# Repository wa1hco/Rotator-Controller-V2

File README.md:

# Rotator-Controller-V2
Designed to remotely control CDE rotors. Updated design with new enclosure and optional user interface

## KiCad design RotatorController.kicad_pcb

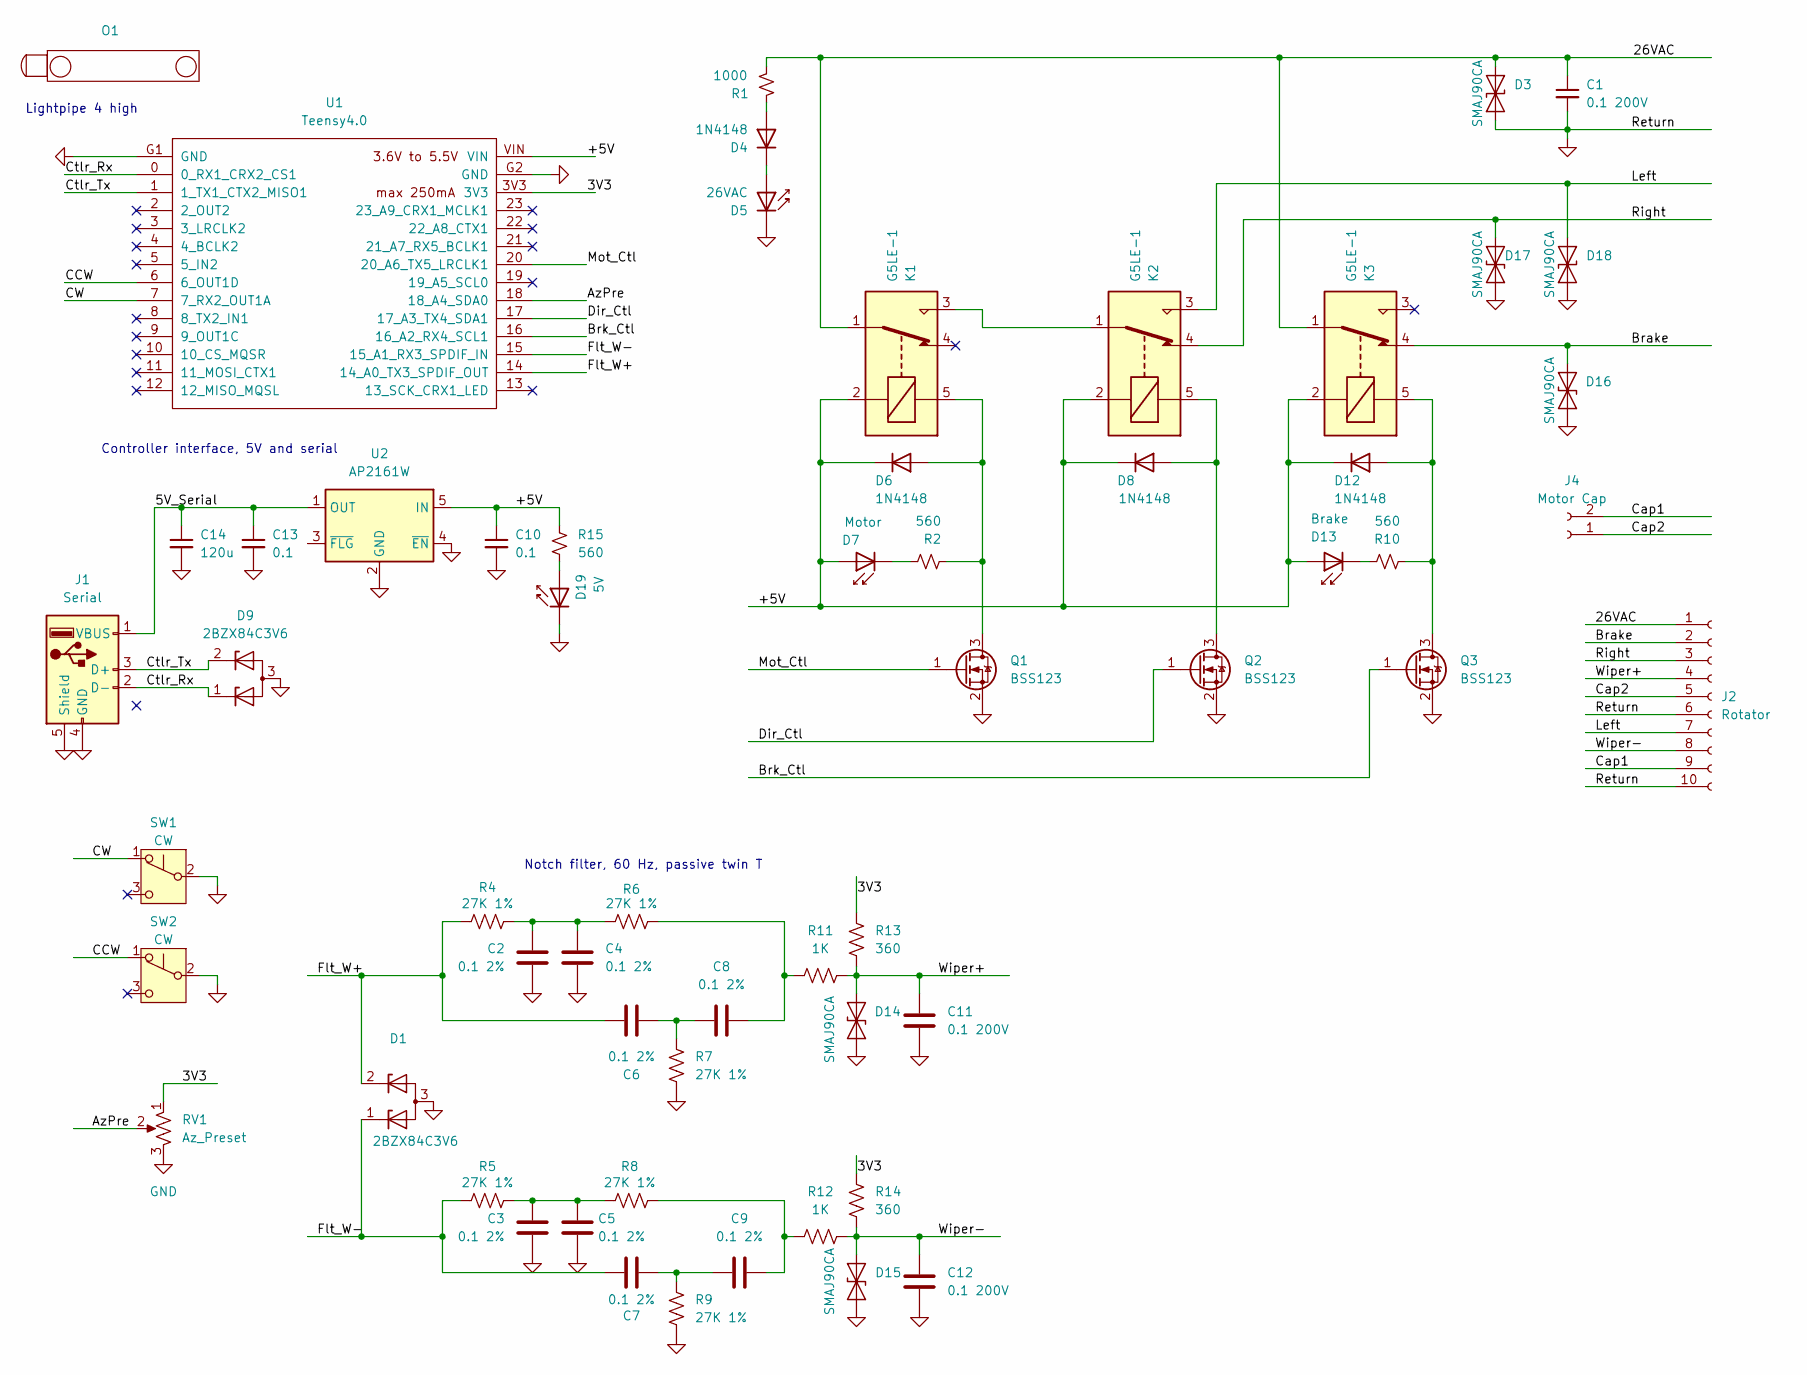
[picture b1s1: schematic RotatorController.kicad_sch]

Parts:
C1, C11, C12: 0.1 200V; C_1206_3216Metric_Pad1.33x1.80mm_HandSolder
C2, C3, C4, C5, C6, C7, C8, C9: 0.1 2%; C_1206_3216Metric_Pad1.33x1.80mm_HandSolder
C10, C13: 0.1; C_1206_3216Metric_Pad1.33x1.80mm_HandSolder
C14: 120u; C_1206_3216Metric_Pad1.33x1.80mm_HandSolder
D1, D9: 2BZX84C3V6; SOT-23
D3, D14, D15, D16, D17, D18: SMAJ90CA; D_SMA
D4, D6, D8, D12: 1N4148; D_SOD-123F
D5: 26VAC; LED_0805_2012Metric
D7: Motor; LED_0805_2012Metric
D13: Brake; LED_0805_2012Metric
D19: 5V; LED_0805_2012Metric
J1: Serial; USB_A_TE_292303-7_Horizontal
J2: Rotator; TE_MATE-N-LOK_1-770971-x_2x05_P4.14mm_Horizontal
J4: Motor Cap; PinHeader_1x02_P2.54mm_Vertical
K1, K2, K3: G5LE-1; Relay_SPDT_Omron-G5LE-1
O1: LP4-EP
Q1, Q2, Q3: BSS123; SOT-23
R1: 1000; R_0805_2012Metric_Pad1.20x1.40mm_HandSolder
R2, R10, R15: 560; R_0805_2012Metric_Pad1.20x1.40mm_HandSolder
R4, R5, R6, R7, R8, R9: 27K 1%; R_0805_2012Metric_Pad1.20x1.40mm_HandSolder
R11, R12: 1K; R_0805_2012Metric_Pad1.20x1.40mm_HandSolder
R13, R14: 360; R_0805_2012Metric_Pad1.20x1.40mm_HandSolder
RV1: Az_Preset; Potentiometer_Alps_RK09K_Single_Horizontal
SW1, SW2: CW; SW_SPST_Omron_B3F-315x_Angled
U1: Teensy4.0; Teensy40_Simple
U2: AP2161W; SOT-23-5

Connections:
/3V3: R13.1, R14.1, RV1.1, U1.3V3
/5V_Serial: C13.1, C14.1, J1.1 (VBUS), U2.1 (OUT)
/26VAC: C1.1, D3.2 (A2), J2.1, K1.1, K3.1, R1.2
/+5V: C10.1, D6.1 (K), D7.2 (A), D8.1 (K), D12.1 (K), D13.2 (A), K1.2, K2.2, K3.2, R15.2, U1.VIN, U2.5 (IN)
/AzPre: RV1.2, U1.18 (18_A4_SDA0)
/Brake: D16.2 (A2), J2.2, K3.4
/Brk_Ctl: Q3.1 (G), U1.16 (16_A2_RX4_SCL1)
/CCW: SW2.1 (A), U1.6 (6_OUT1D)
/CW: SW1.1 (A), U1.7 (7_RX2_OUT1A)
/Cap1: J2.9, J4.2
/Cap2: J2.5, J4.1
/Ctlr_Rx: D9.1 (K), J1.2 (D-), U1.0 (0_RX1_CRX2_CS1)
/Ctlr_Tx: D9.2 (K), J1.3 (D+), U1.1 (1_TX1_CTX2_MISO1)
/Dir_Ctl: Q2.1 (G), U1.17 (17_A3_TX4_SDA1)
/Flt_W+: C6.1, D1.2 (K), R4.1, U1.14 (14_A0_TX3_SPDIF_OUT)
/Flt_W-: C7.1, D1.1 (K), R5.1, U1.15 (15_A1_RX3_SPDIF_IN)
/Left: D18.2 (A2), J2.7, K2.3
/Mot_Ctl: Q1.1 (G), U1.20 (20_A6_TX5_LRCLK1)
/Right: D17.2 (A2), J2.3, K2.4
/Wiper+: C11.2, D14.2 (A2), J2.4, R11.2, R13.2
/Wiper-: C12.2, D15.2 (A2), J2.8, R12.2, R14.2
GND: C1.2, C2.2, C3.2, C4.2, C5.2, C10.2, C11.1, C12.1, C13.2, C14.2, D1.3 (A), D3.1 (A1), D5.1 (K), D9.3 (A), D14.1 (A1), D15.1 (A1), D16.1 (A1), D17.1 (A1), D18.1 (A1), D19.1 (K), J1.4 (GND), J1.5 (Shield), J2.6, J2.10, Q1.2 (S), Q2.2 (S), Q3.2 (S), R7.2, R9.2, RV1.3, SW1.2 (B), SW2.2 (B), U1.G1 (GND), U1.G2 (GND), U2.2 (GND), U2.4 (~EN)
unnamed: C2.1, C4.1, R4.2, R6.1
unnamed: C3.1, C5.1, R5.2, R8.1
unnamed: C6.2, C8.1, R7.1
unnamed: C7.2, C9.1, R9.1
unnamed: C8.2, R6.2, R11.1
unnamed: C9.2, R8.2, R12.1
unnamed: D4.2 (A), R1.1
unnamed: D4.1 (K), D5.2 (A)
unnamed: D6.2 (A), K1.5, Q1.3 (D), R2.2
unnamed: D7.1 (K), R2.1
unnamed: D8.2 (A), K2.5, Q2.3 (D)
unnamed: D12.2 (A), K3.5, Q3.3 (D), R10.2
unnamed: D13.1 (K), R10.1
unnamed: D19.2 (A), R15.1
unnamed: K1.3, K2.1

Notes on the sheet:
Controller interface, 5V and serial
Lightpipe 4 high
Notch filter, 60 Hz, passive twin T

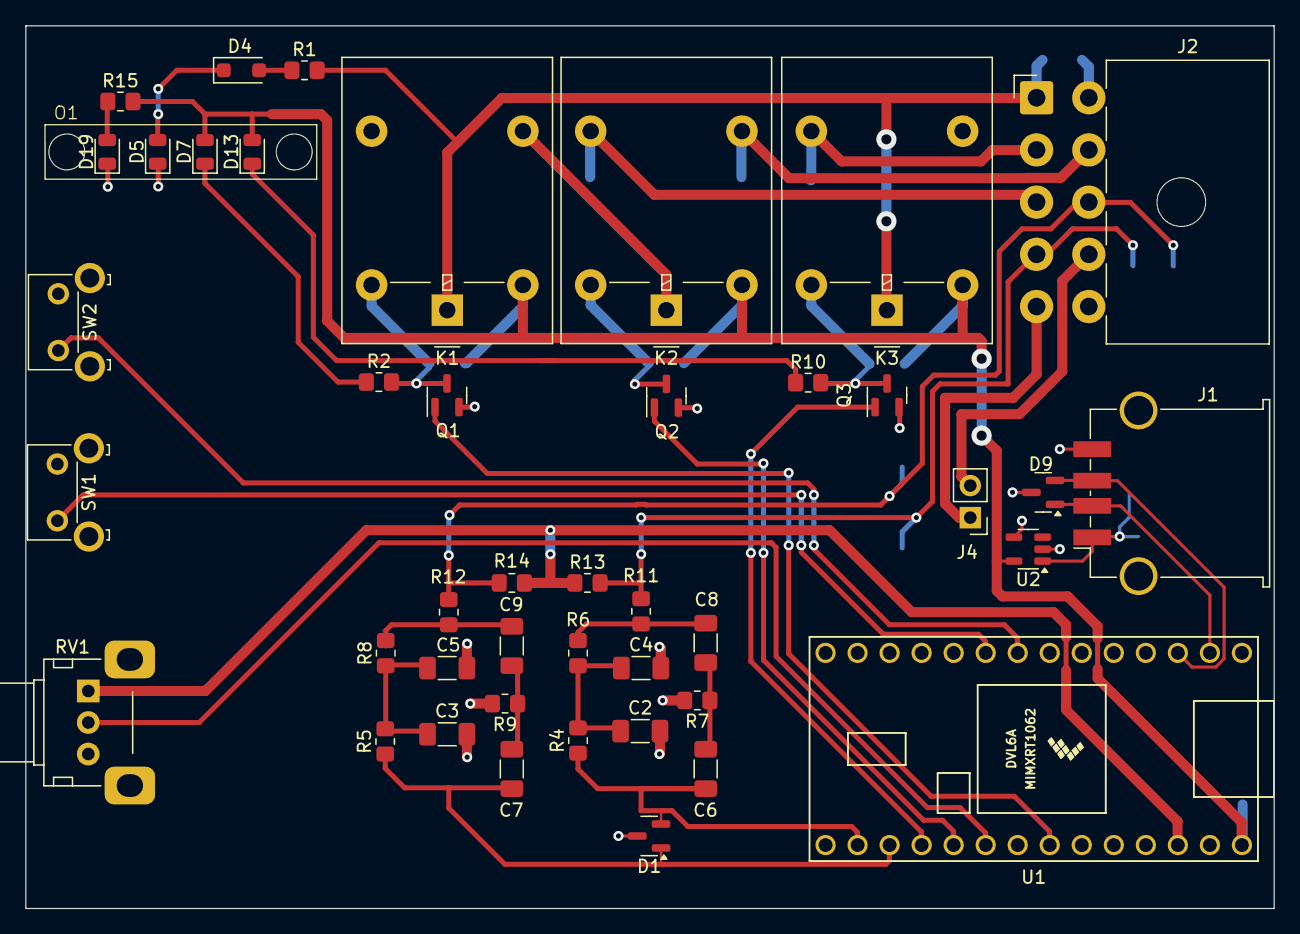
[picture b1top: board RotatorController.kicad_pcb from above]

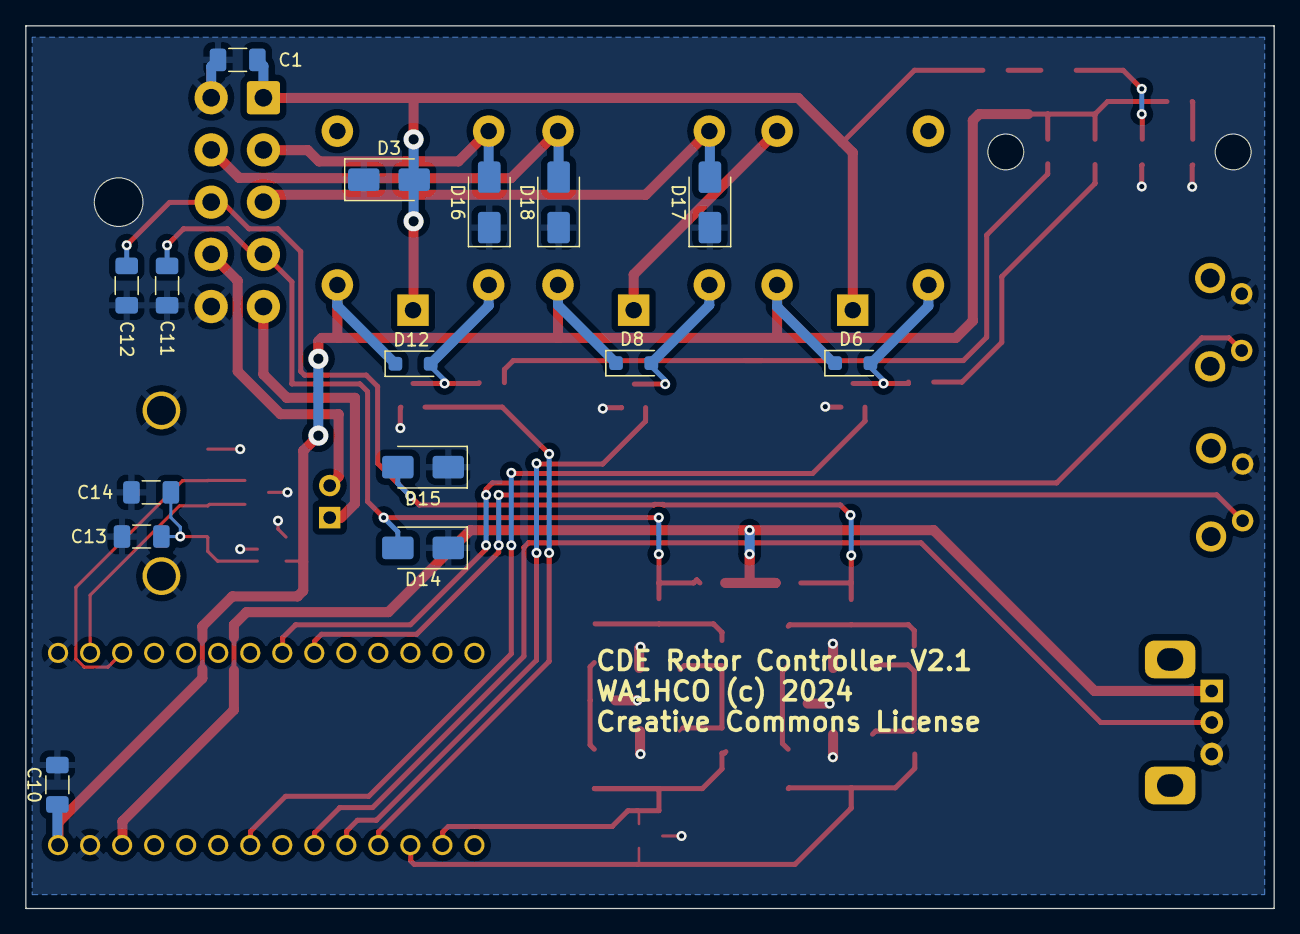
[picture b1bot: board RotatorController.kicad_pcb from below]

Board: 2 copper layers, 99.0 x 70.0 mm, 59 parts (15 on the bottom side), 37 nets.

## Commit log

2024-06-20 Initial commit of KiCAD files, sorting .gitigore and other initial stuff
2024-06-20 Moved some components to back side Update precision cap footprint from 1210 to 1206 Added board ID, (c), and license text Streamlined interconnect by connecting some TH pins via back side
2024-06-20 Added files Update board outline based on measurements Moved connectors to new board outline
2024-06-21 Moved Teensy into position, adjusted related traces
2024-06-26 Mid layout of smaller pcb with separately mounted cap still need to assign cap connector Added 4 high light pipe and 0805 LEDs, need to create footprint
2024-06-27 Added light pipe footprint Completed layout and deisgn rule check
2024-06-27 Simplified symbol and footprint for Teensy4.0 to remove unused pins Corrected error where footprints reverted to through-hole (mystery)
2024-06-28 Added OSHPark pcb design rules fixed a few design rule checks
2024-06-29 Moved relays and lightpipe to make room for motor cap mounted over PCB
2024-06-29 Board dimensions in inches tweaked layout
2024-07-14 Homing in on final release add ground to pot and button mounting pads added start of dimensions and front panel sketch
2024-07-15 dimensioned drawings of front and back panels corrected switch and pot parts moved connectors and switches to flush with end of board
2024-07-15 fine tuned layout to shorten bypass cap ground and to reduce ground plane breaks
2024-07-15 Removing old backups
2024-07-23 Branch "Inline" created. Support this controller inline between manual control box and rotator.
2024-07-26 Clean up duplicates in datasheets, rename for clarity
2024-07-26 finish cleanup of deleted and renamed datasheets, stage and commits trivial changes to pcb and sch
2024-08-28 added tag for release, KiCAD updated the dates, but no intended changes
2024-08-29 Moved library into project directory due to permission problem
2024-08-29 Created V3 branch for new board with 3.6V zeners for protection
2025-09-28 Merged software from V2 Started looking at using STM32 series MCU instead of teensy
2025-09-30 More work on schematic Started software conversion to STM32F405 MCU
2025-10-09 Removed some deleted files

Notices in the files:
RotatorController.kicad_pcb:
WA1HCO (c) 2024
Creative Commons License
